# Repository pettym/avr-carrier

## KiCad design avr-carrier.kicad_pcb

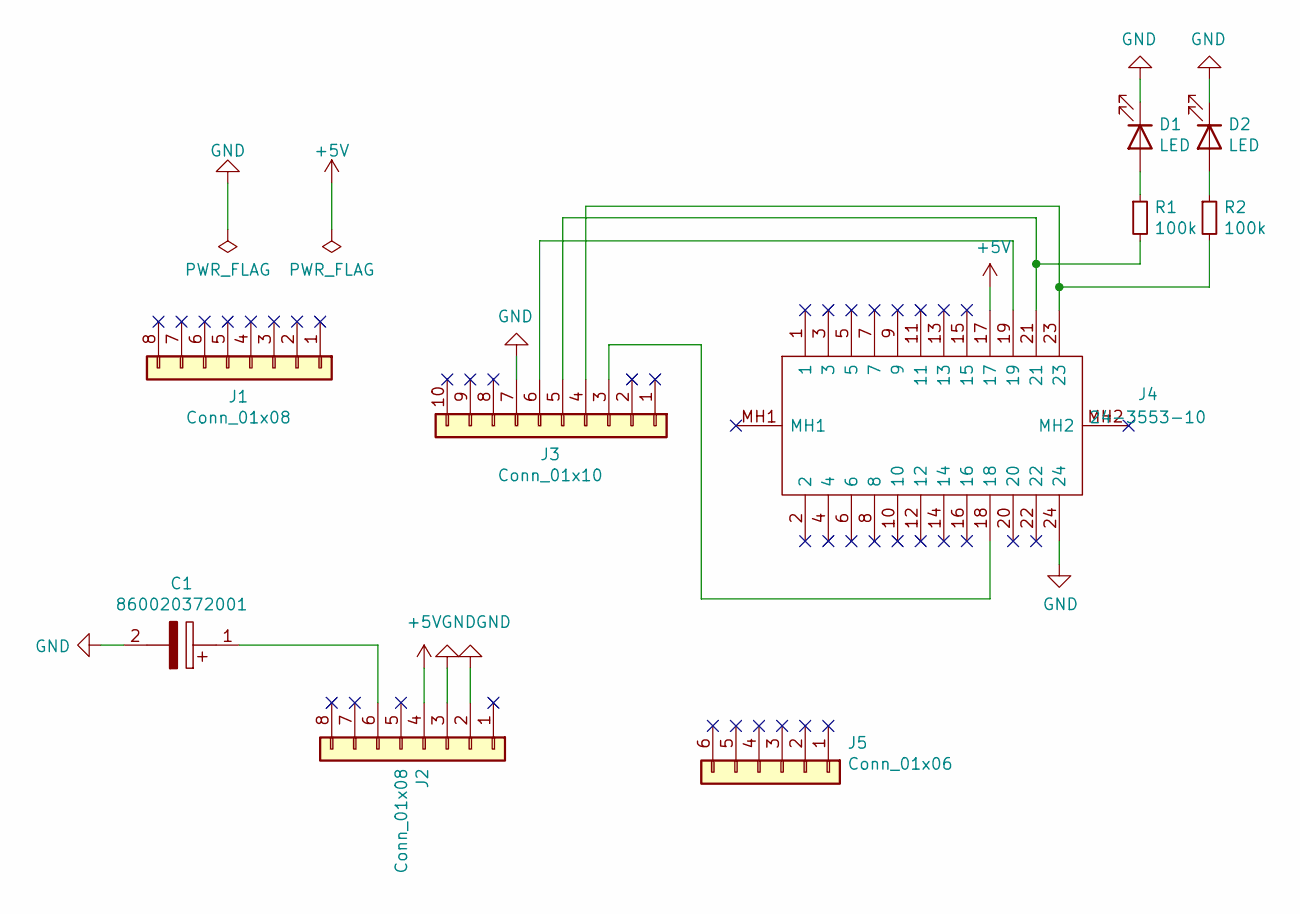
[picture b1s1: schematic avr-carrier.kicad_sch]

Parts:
C1: 860020372001; CAPPRD200W52D500H1250; Mouser Part Number 710-860020372001
D1, D2: LED; LTL4232
J1, J2: Conn_01x08; PinHeader_1x08_P2.54mm_Vertical
J3: Conn_01x10; PinHeader_1x10_P2.54mm_Vertical
J4: 24-3553-10; 24355310; Mouser Part Number 535-24-3553-10
J5: Conn_01x06; PinHeader_1x06_P2.54mm_Vertical
R1, R2: 100k; RESAD1100W50L340D190

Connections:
+5V: J1.17, J2.4, J4.17
GND: C1.2, D1.1 (K), D2.1 (K), J1.24, J2.2, J2.3, J3.7, J4.24
unnamed: C1.1, J2.6
unnamed: D1.2 (A), R1.1
unnamed: D2.2 (A), R2.1
unnamed: J1.18, J3.3, J4.18
unnamed: J1.23, J3.4, J4.23, R2.2
unnamed: J1.21, J3.5, J4.21, R1.2
unnamed: J1.19, J3.6, J4.19

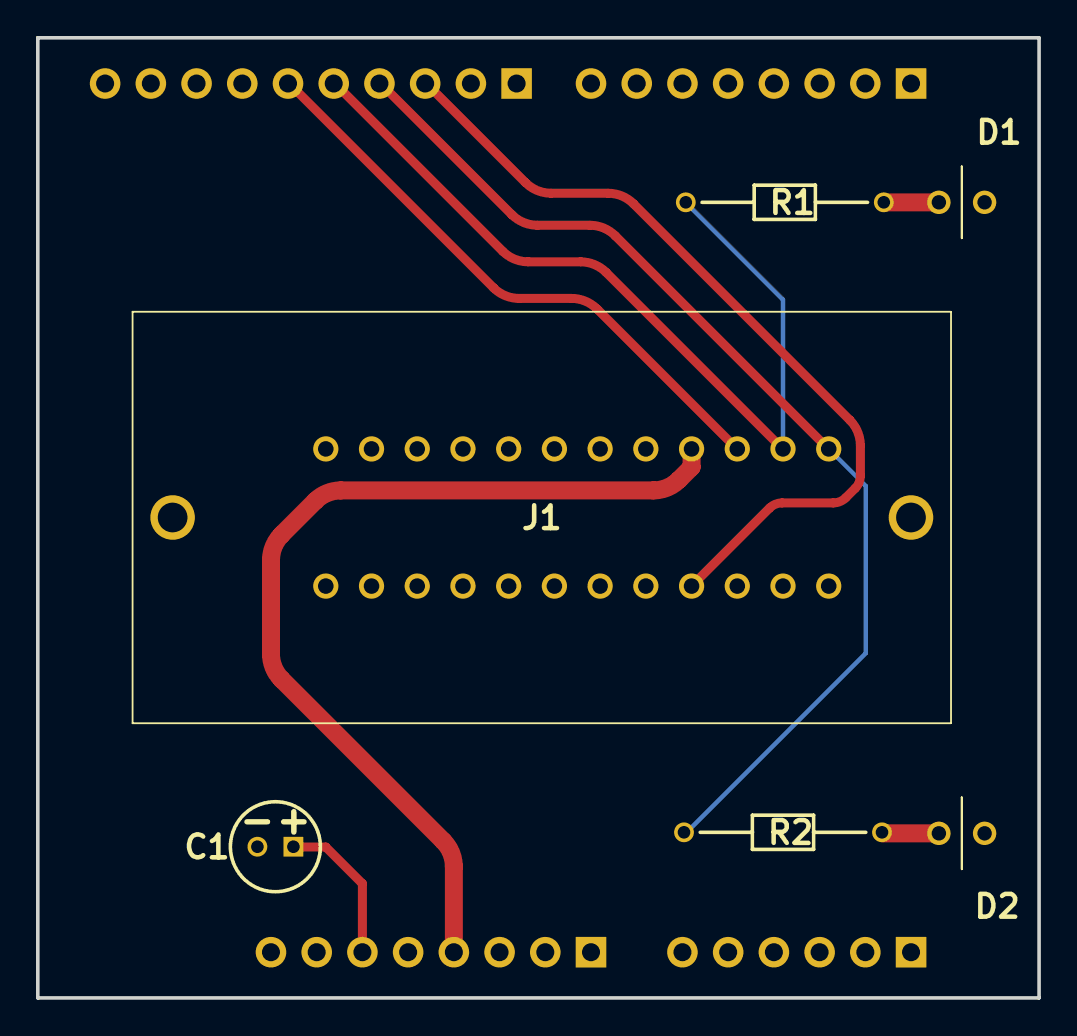
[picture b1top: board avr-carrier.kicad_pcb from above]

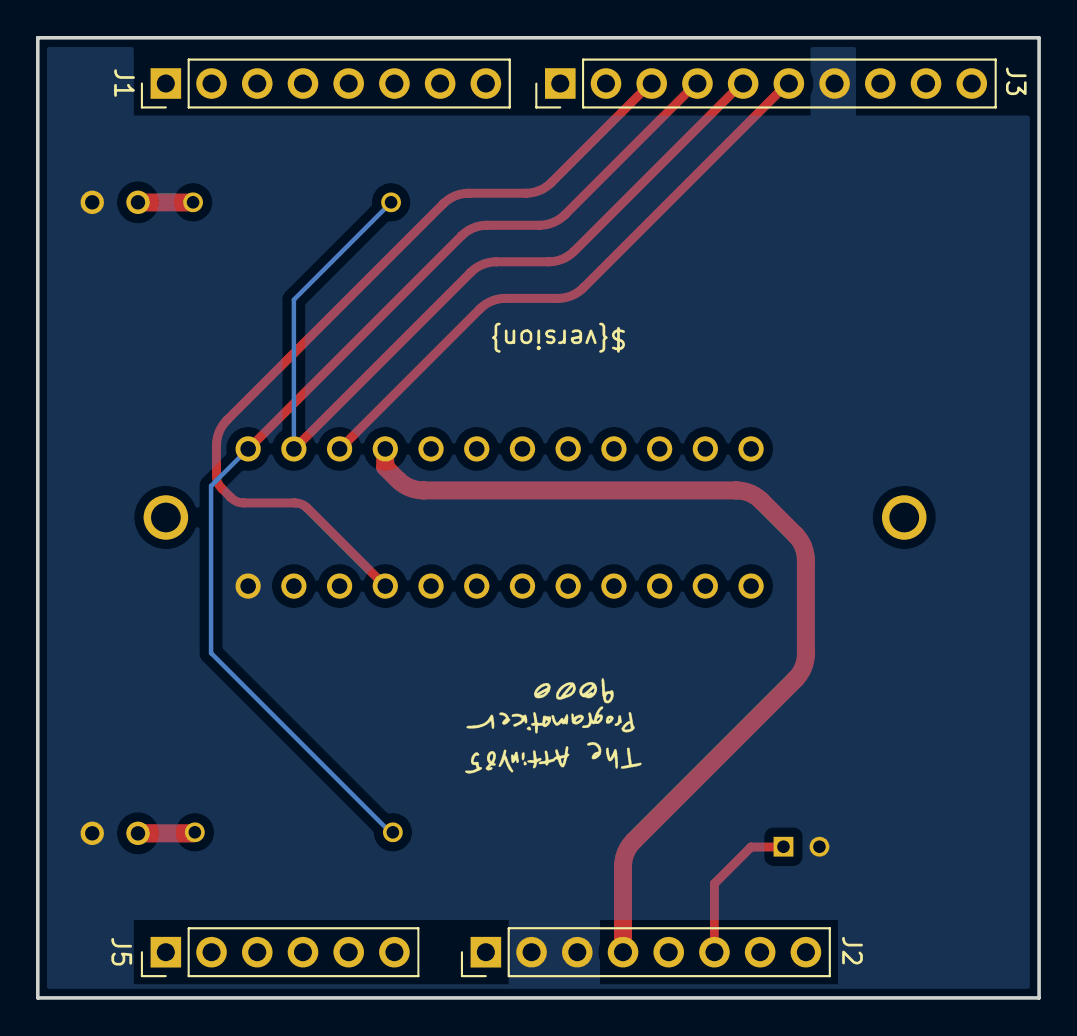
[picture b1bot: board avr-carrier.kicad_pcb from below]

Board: 2 copper layers, 55.6 x 53.3 mm, 10 parts (4 on the bottom side), 9 nets.

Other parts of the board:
J1#2: Conn_01x08; PinHeader_1x08_P2.54mm_Vertical

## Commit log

2023-06-02 init
2024-05-09 use other workflow
2024-05-12 stuff
2024-05-12 fix everything
2024-05-12 fix rules
2024-05-12 fix drc warnings
2024-05-12 slight fixing
